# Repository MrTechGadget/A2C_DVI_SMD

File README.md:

# A2CDVI_SMD

This is a project for a digital DVI/HDMI video cards for Apple IIc or IIc+. It directly produces a digital video stream from the Apple IIc's digital video output connector. The signal is output via an HDMI connector, connecting the Apple IIc to modern displays with HDMI (or DVI) inputs. No more analog signal conversion required.

## BACKGROUND
### Mike Neil's [Inspiration](https://github.com/FarLeftLane/A2C_DVI_Board)
> I have been working on a project using an ESP32-C6 to take the digital video signals from the Apple IIc DB15 video connector and allow remote viewing of the screen on a PC (watch this account for the ViewIIc plans).  The circuit design was pretty simple, a DB15 connector, a 74VLC245 for level conversion (5V to 3.3V) and a ESP32-C6 module. It occured to me that I could take those same Apple IIc signals and using the picoDVI libraries create a IIc to HDMI solution using an RP2040 or RP2350 (Raspberry Pi Pico). This is the same HW that is on an A2DVI card for a slotted Apple II (RP2040 and 245's). The Protype takes the A2DVI card out of the machine and instead of connecting to Apple II bus signals (address, data, etc), we feed the Apple IIc digital video signals into the cards pins and use custom firmware to recreate the display out to HDMI.

## HARDWARE
### Protoype

My first version was designed from Mike's schematic and mapping those through the the needed components found on the A2DVI card itself. It utilized a Raspberry Pi Pico device for simplicity, but the overall size was too big and it blocked access to the composite video

### Version 2

Inspired by the working prototype, I decided I could make it MUCH smaller by implementing the RP2040 directly on the board. 

### Version 2.5

Fixed compatibility issues with some HDTVs and added hardware support for Mike Neil's latest firmware features!

## Availability

This card is available for purchase in the US for $35 plus shipping on my Tindie Store [MrTechGadget's Gadgets](https://www.tindie.com/products/mrtechgadget/a2cdvi/)

## Flashing Firmware
The latest firmware can be found on Mike Neil's [A2C_DVI_Firmware repo](https://github.com/FarLeftLane/A2C_DVI_Firmware/tree/master/Releases)

To load the firmware use a microUSB cable to your PC/Mac with the A2CDVI card plugged into the Apple IIc. It is the exact same process as flashing a Raspberry Pi Pico. There is a small BOOTSEL button in the middle of the board close to the DA15 connector, above the word HOTPLUG.  Hold that button down, and while holding it, plug the USB cable into your PC/Mac.  You should see a volume appear on the PC/Mac.  Copy the "A2C_DVI_v1.7.6.uf2" file to this volume and the card should update and reboot.   If you have a HDMI monitor attached to the card, you should see the A2C_DVI splash screen.  Unplug the card from USB.  Never Hotplug the DA15 connector to the Apple IIc.

**SPECIAL THANKS**

- Mike Neil ( https://github.com/FarLeftLane/ )
- Ralle Palaveev ( https://github.com/rallepalaveev/A2DVI )
- Thorsten Brehm ( https://github.com/ThorstenBr/A2DVI-Firmware )
- David Kuder ( https://github.com/V2RetroComputing/analog )

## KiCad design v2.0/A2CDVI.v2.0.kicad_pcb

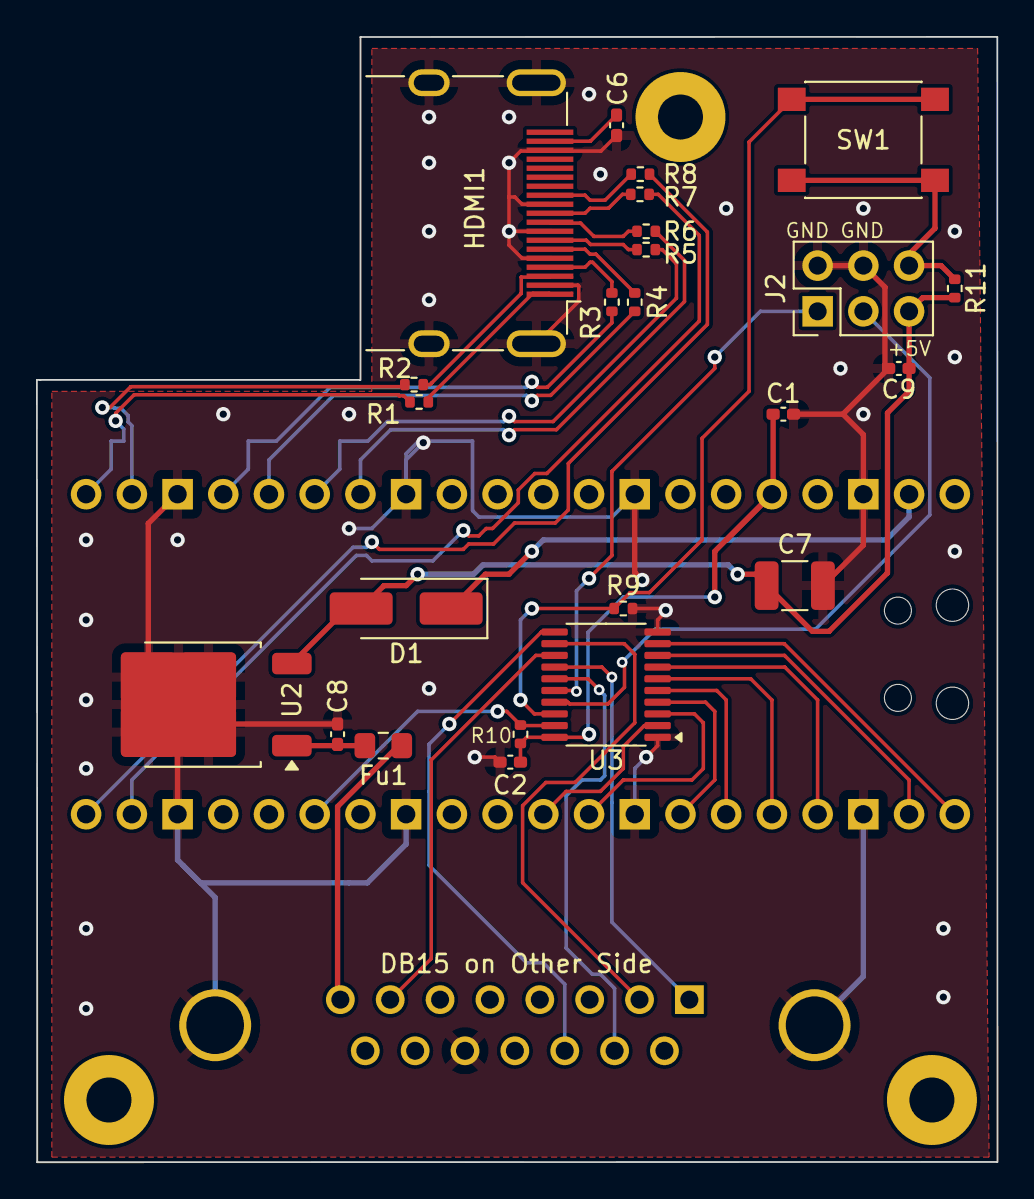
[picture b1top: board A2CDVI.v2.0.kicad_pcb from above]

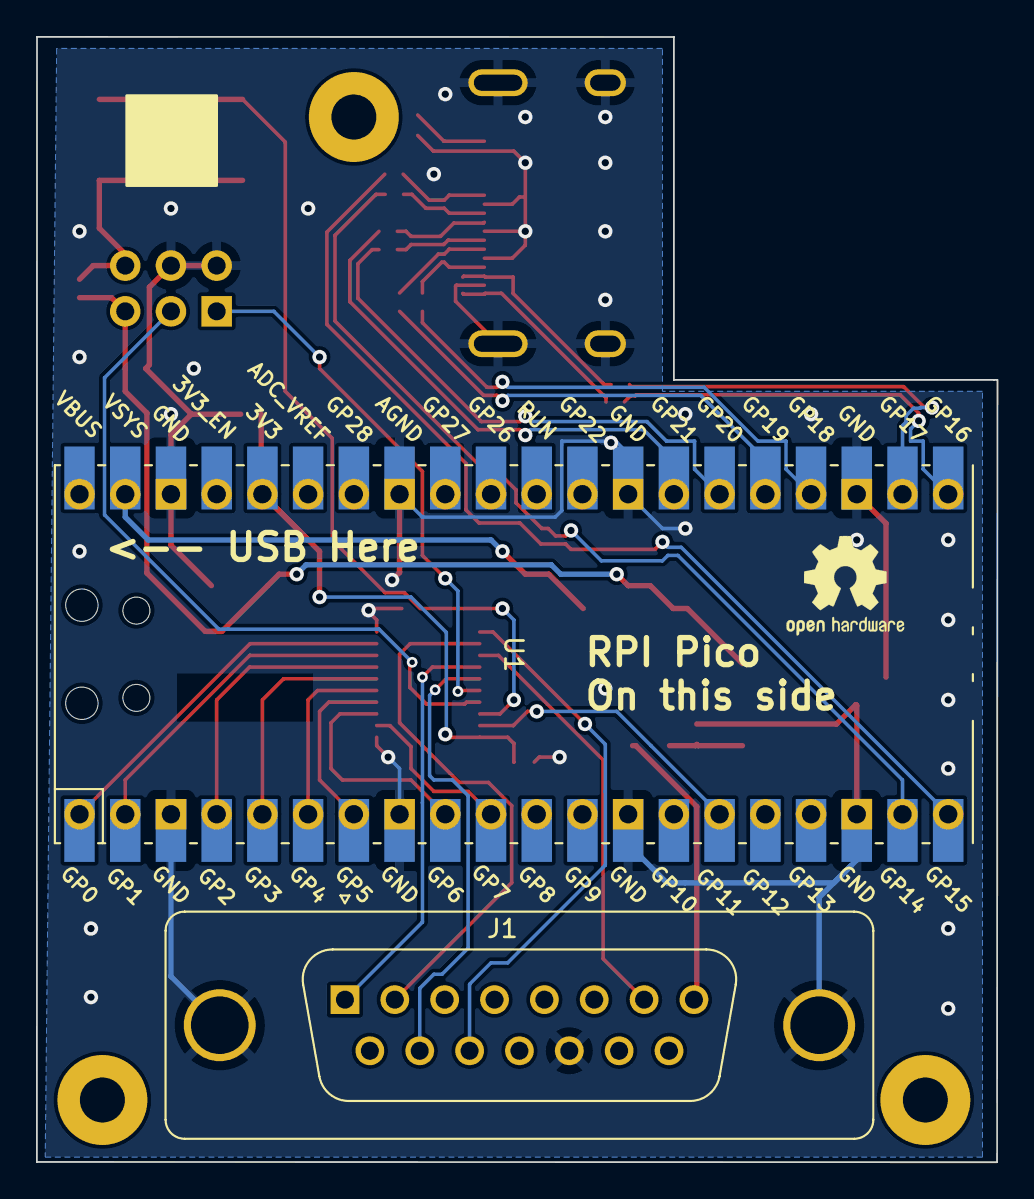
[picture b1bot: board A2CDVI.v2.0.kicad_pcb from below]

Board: 2 copper layers, 53.4 x 62.5 mm, 26 parts (2 on the bottom side), 33 nets.

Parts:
C1, C2, C6: 100n; C_0402_1005Metric_Pad0.74x0.62mm_HandSolder
C7: 220u; C_1210_3225Metric_Pad1.33x2.70mm_HandSolder
C8, C9: C; C_0402_1005Metric_Pad0.74x0.62mm_HandSolder
D1: MBR120VLSFT1G; D_SMA_Handsoldering
Fu1: Polyfuse 100mA; Fuse_0805_2012Metric_Pad1.15x1.40mm_HandSolder
HDMI1: HDMI-SWM-19; HDMI_A_Molex_208658-1001_Horizontal
J1: DA15_Plug; DSUB-15_Male_Vertical_P2.77x2.84mm_MountingHoles
J2: Aux; PinHeader_2x03_P2.54mm_Vertical
R1, R2, R3, R4, R5, R6, R7, R8: 270; R_0402_1005Metric
R9: 10k; R_0402_1005Metric
R10: 10K; R_0402_1005Metric
R11: 1k; R_0402_1005Metric
SW1: Config; SW_SPST_PTS645
U1: RPI-Pico; RPi_Pico_SMD_TH_NO_DEBUG
U2: L7805; TO-252-2
U3: 74LVC245; TSSOP-20_4.4x6.5mm_P0.65mm

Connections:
+3V3: C1.1, C2.1, R10.1, U1.36 (3V3), U3.20 (VCC)
+5V: C7.1, C9.1, D1.2 (A), J2.5, R11.2, U2.3 (OUT)
+12V: C8.1, Fu1.2, U2.1 (IN)
/CK+: HDMI1.10, R7.1, R7.2, U1.19 (GP14)
/CK-: HDMI1.12, R8.1, R8.2, U1.20 (GP15)
/D0+: HDMI1.7, R5.1, R5.2, U1.26 (GP20)
/D0-: HDMI1.9, R6.1, R6.2, U1.27 (GP21)
/D1+: HDMI1.4, R3.1, R3.2, U1.24 (GP18)
/D1-: HDMI1.6, R4.1, R4.2, U1.25 (GP19)
/D2+: HDMI1.1, R1.1, R1.2, U1.21 (GP16)
/D2-: HDMI1.3, R2.1, R2.2, U1.22 (GP17)
GND: C1.2, C2.2, C6.2, C7.2, C8.2, C9.2, HDMI1.2, HDMI1.5, HDMI1.8, HDMI1.11, HDMI1.17, HDMI1.GND, J1.0, J1.13 (GND), J2.2, J2.4, R9.2, U1.3 (GND), U1.8 (GND), U1.13 (GND), U1.18 (GND), U1.23 (GND), U1.28 (GND), U1.33 (GND), U1.38 (GND), U2.2 (GND), U3.1 (A->B), U3.10 (GND)
unnamed: C6.1, HDMI1.18
unnamed: D1.1 (K), U1.39 (VSYS)
unnamed: J1.2 (14M), U3.12 (B6)
unnamed: Fu1.1, J1.8 (+12V)
unnamed: J1.10 (GR), U3.15 (B3)
unnamed: J1.11 (SEROUT), U3.11 (B7)
unnamed: J1.1 (TEXT), U3.14 (B4)
unnamed: J1.7 (WNDW), U3.13 (B5)
unnamed: J2.1, U3.16 (B2)
unnamed: J2.3, U3.17 (B1)
unnamed: J2.6, R11.1, SW1.1
unnamed: U1.1 (GP0), U3.9 (A7)
unnamed: U1.2 (GP1), U3.8 (A6)
unnamed: U1.4 (GP2), U3.7 (A5)
unnamed: U1.5 (GP3), U3.6 (A4)
unnamed: U1.6 (GP4), U3.5 (A3)
unnamed: U1.7 (GP5), U3.4 (A2)
unnamed: U1.9 (GP6), U3.3 (A1)
unnamed: U1.10 (GP7), U3.2 (A0)
unnamed: R10.2, U1.15 (GP11), U3.19 (CE)
unnamed: R9.1, SW1.2, U3.18 (B0)

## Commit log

2025-04-18 Starting Schematic
2025-04-18 Update A2CDVI.v2.0.kicad_sch
    Added components, removed Slot and extra 245 chips
2025-04-19 Initial Layout mess
2025-04-21 Basic Board Layout
2025-04-26 Tracks drawn
2025-04-26 Ready for v1
2025-04-26 Fixed missing connections in schematic
2025-04-26 Fixed DRC issues
2025-06-11 Update README.md
    First significant update to README for public release
2025-06-11 Update README.md
    Added Tindie Link
2025-06-11 Add board image
2025-06-11 Update README.md
    Add image
2025-06-30 Added Case Files
2025-06-30 Add photo
2025-10-23 Updated Case design for better connection
    This case is easier to print and has better retention in the DA15 video port on the Apple IIc

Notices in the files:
v2.0/A2CDVI.v2.0.kicad_pcb:
Board design by
Josh Clark, (c) 2025
